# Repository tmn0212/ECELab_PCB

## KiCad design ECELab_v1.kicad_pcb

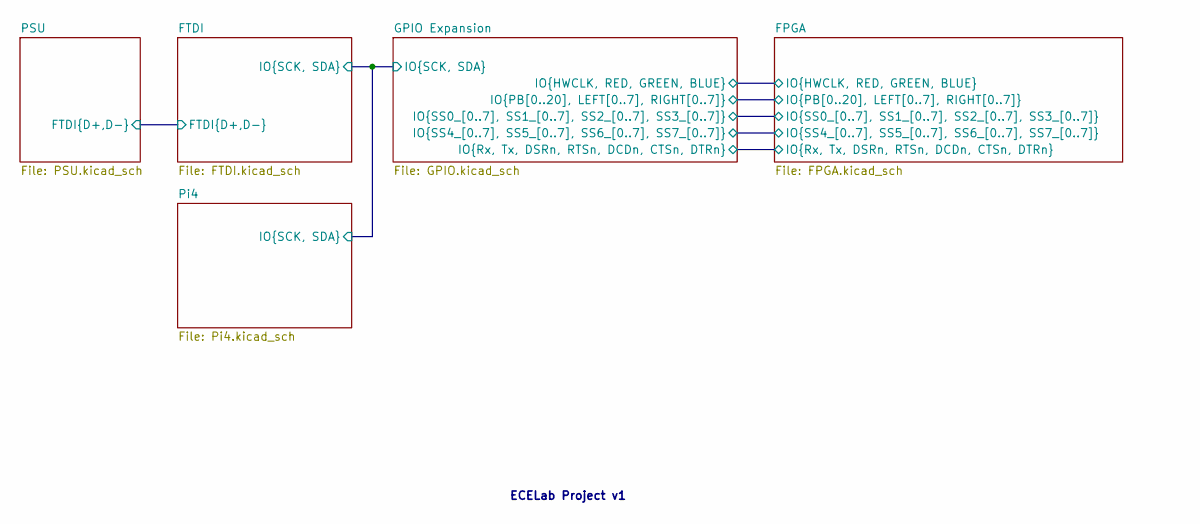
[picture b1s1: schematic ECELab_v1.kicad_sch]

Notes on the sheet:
ECELab Project v1

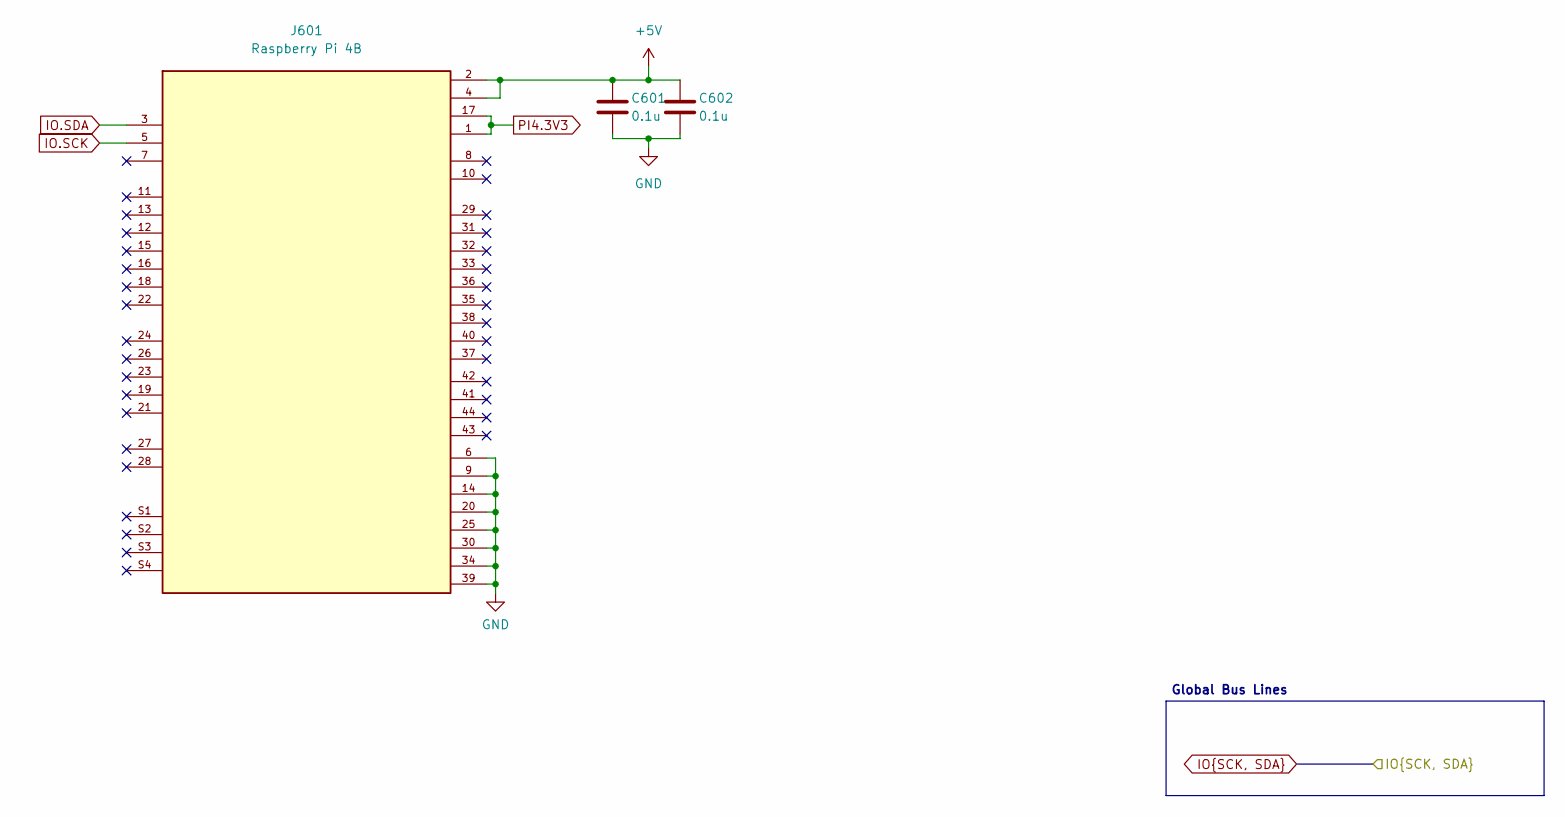
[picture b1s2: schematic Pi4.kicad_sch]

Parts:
C601, C602: 0.1u; C_0402_1005Metric; LCSC Part Number C1525
J601: Raspberry Pi 4B; PinSocket_2x20_P2.54mm_Vertical; LCSC C2977589

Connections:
+5V: C601.1, C602.1, J601.2 (5V), J601.4 (5V); also elsewhere on the board
GND: C601.2, C602.2, J601.6 (GND), J601.9 (GND), J601.14 (GND), J601.20 (GND), J601.25 (GND), J601.30 (GND), J601.34 (GND), J601.39 (GND); also elsewhere on the board
IO.SCK: J601.5 (GPIO3/SCL1); also elsewhere on the board
IO.SDA: J601.3 (GPIO2/SDA1); also elsewhere on the board
PI4.3V3: J601.1 (3V3), J601.17 (3V3); also elsewhere on the board

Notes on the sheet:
Global Bus Lines

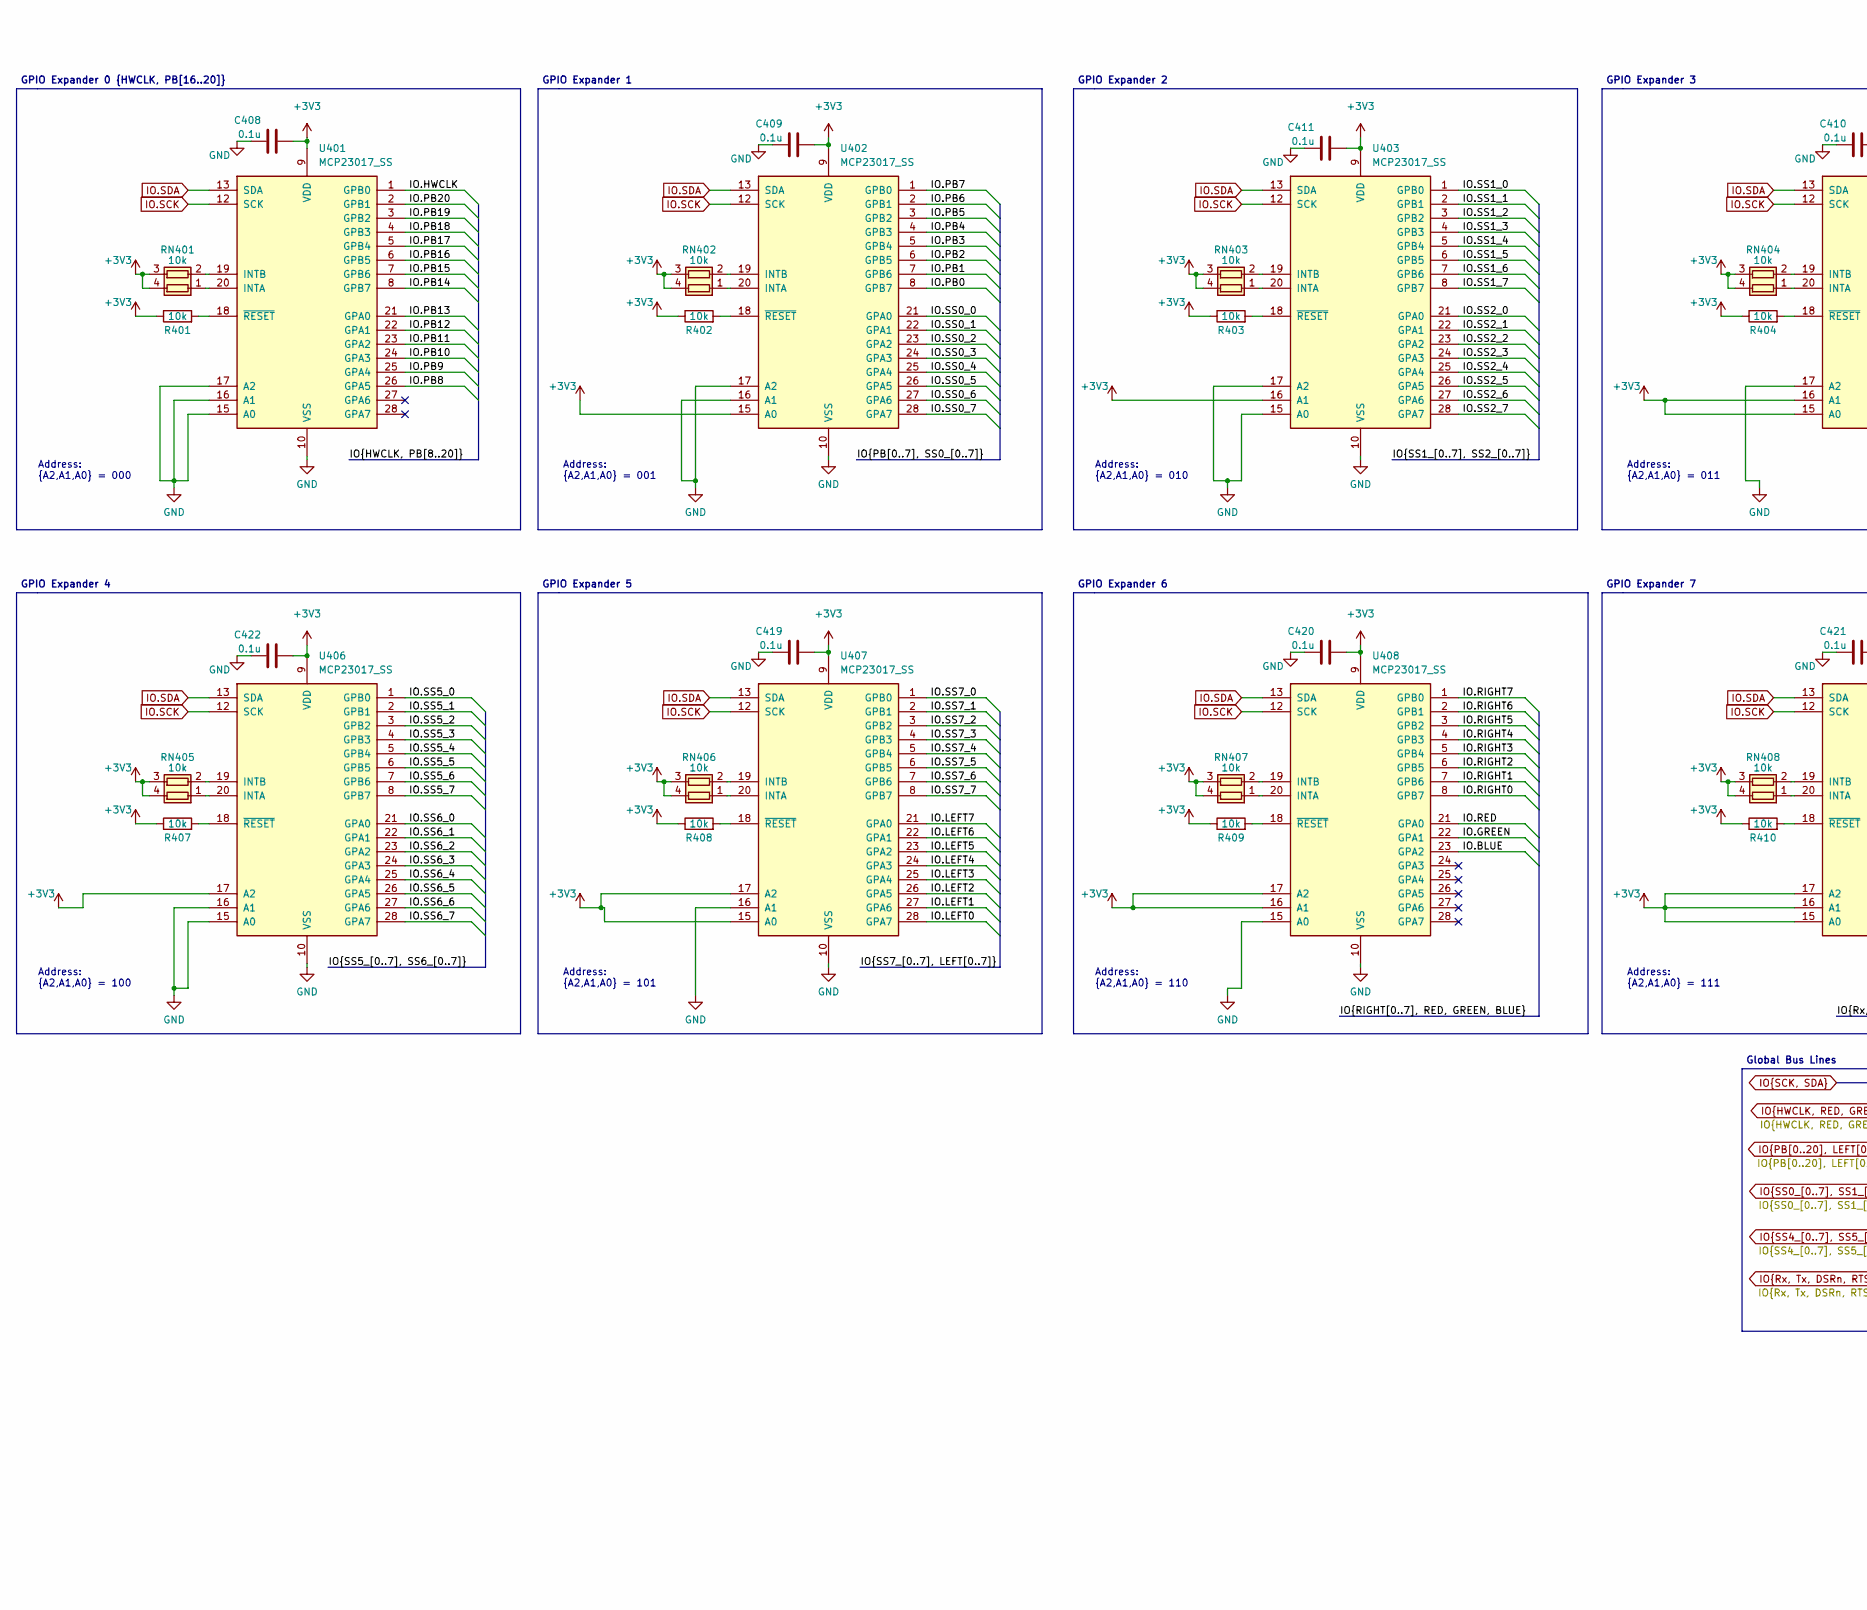
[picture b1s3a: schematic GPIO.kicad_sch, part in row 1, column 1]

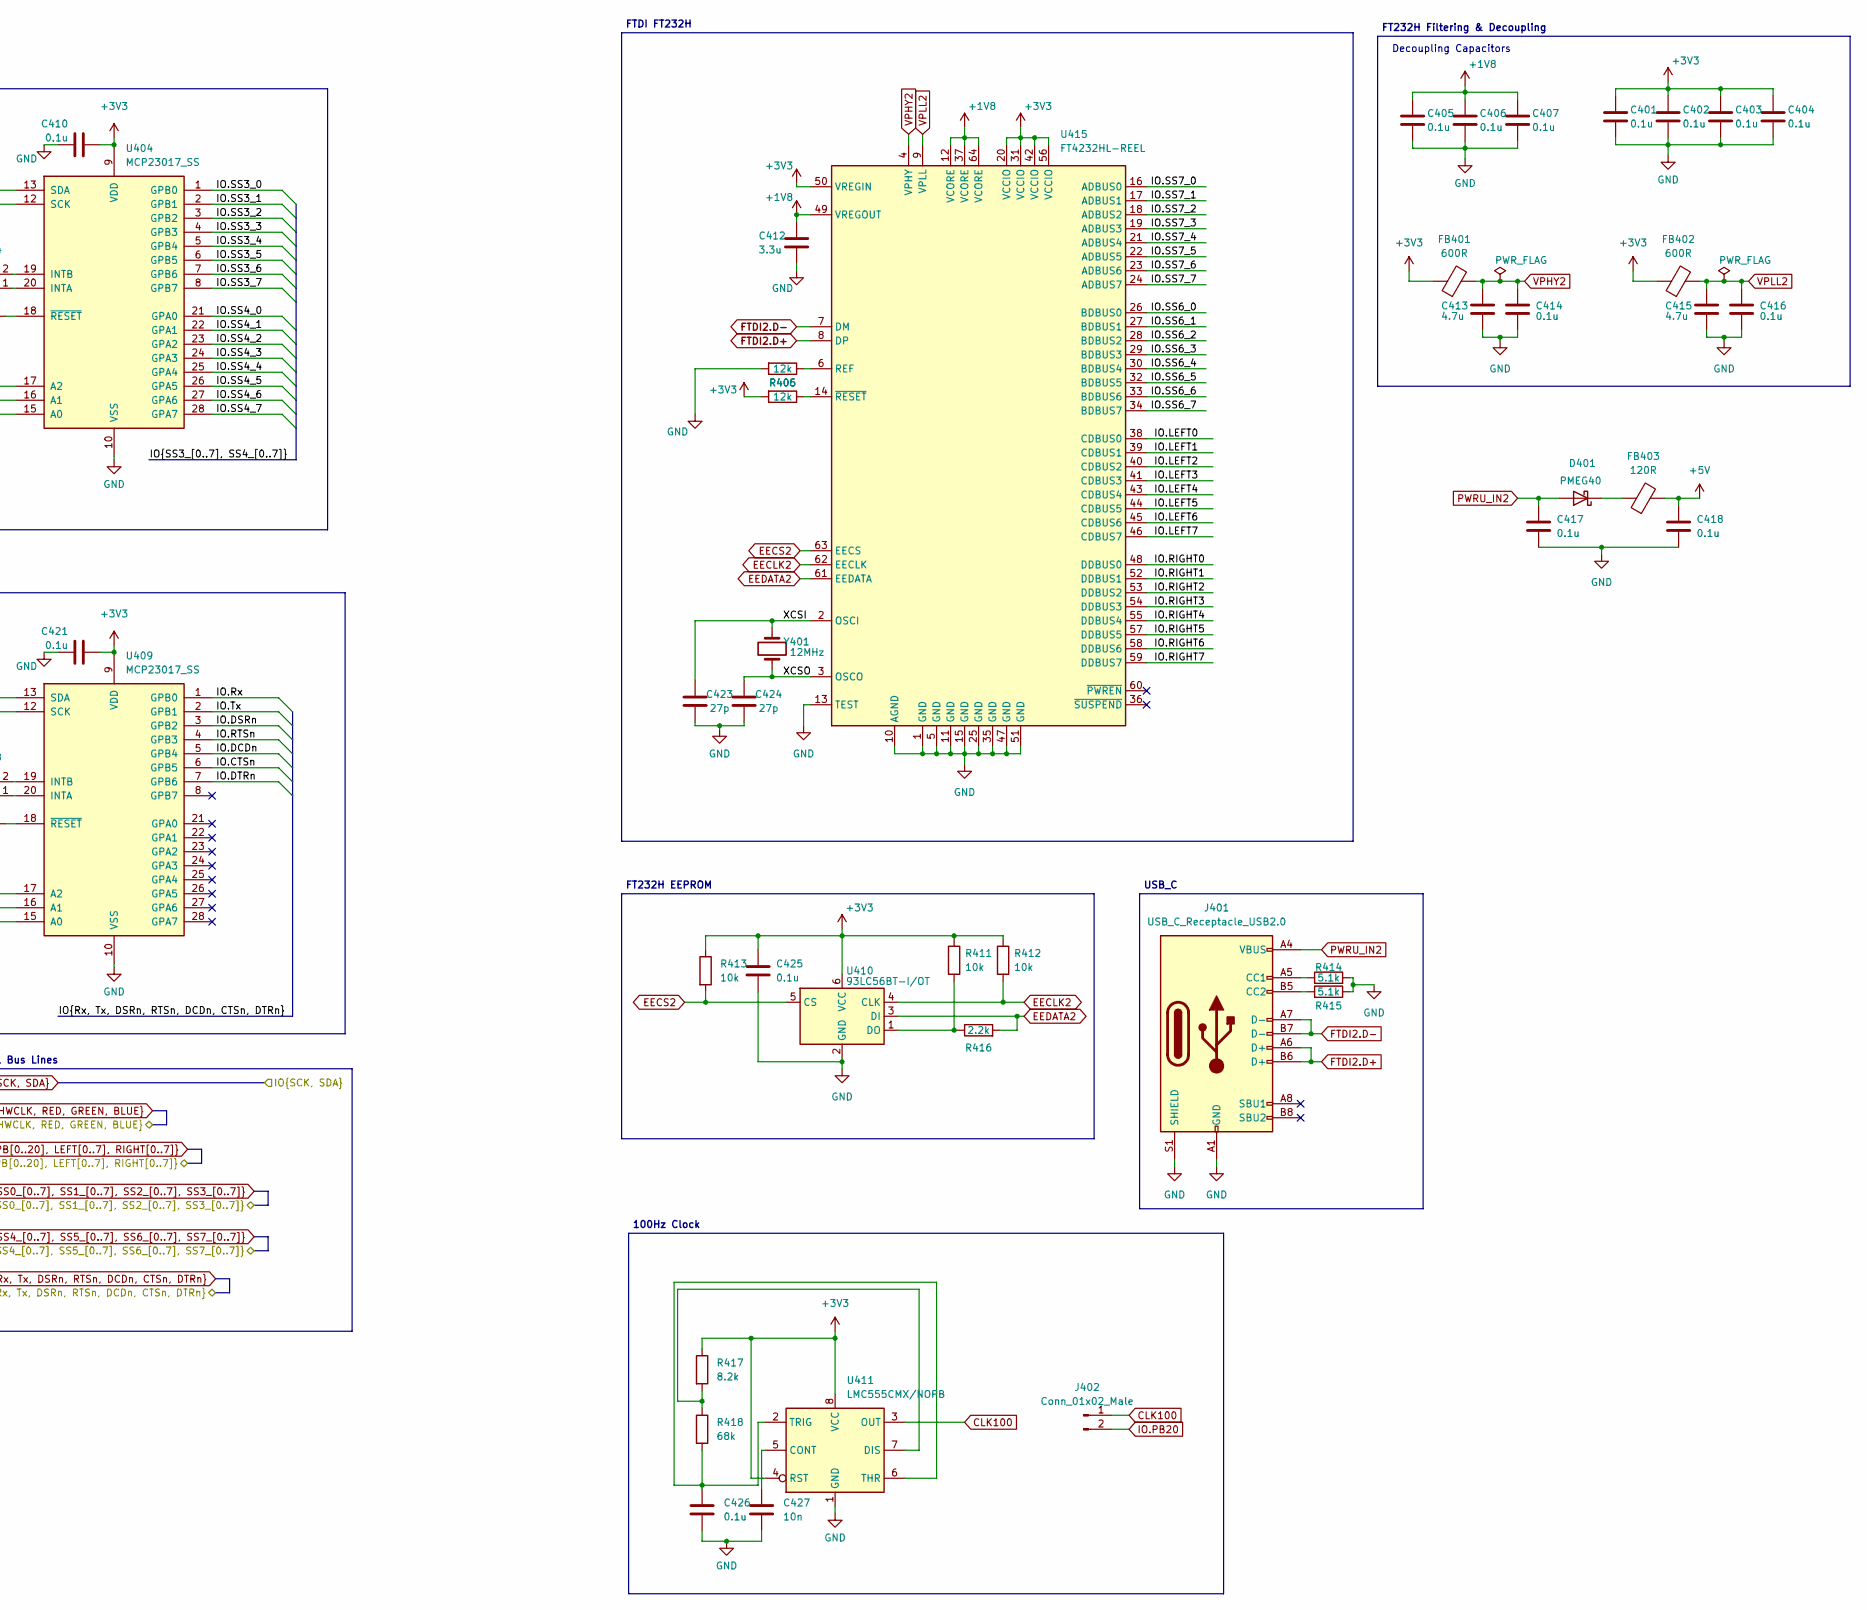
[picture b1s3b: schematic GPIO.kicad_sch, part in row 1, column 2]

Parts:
C401, C402, C403, C404, C405, C406, C407, C408, C409, C410, C411, C417, C418, C419, C420, C421, C422: 0.1u; C_0402_1005Metric; LCSC Part Number C1525
C412: 3.3u; C_0402_1005Metric; LCSC C694161
C413, C415: 4.7u; C_0402_1005Metric; LCSC C368809
C414, C416, C425, C426: 0.1u; C_0402_1005Metric; LCSC C1525
C423, C424: 27p; C_0402_1005Metric; LCSC Part Number C1557
C427: 10n; C_0402_1005Metric; LCSC C60133
D401: PMEG40; D_SOD-323; LCSC Part Number C36975
FB401, FB402: 600R; L_0603_1608Metric; LCSC Part Number C1002
FB403: 120R; L_0603_1608Metric; LCSC Part Number C279682
J401: USB_C_Receptacle_USB2.0; USB_C_Receptacle_HRO_TYPE-C-31-M-12; LCSC Part Number C165948
J402: Conn_01x02_Male; PinHeader_1x02_P2.54mm_Vertical; LCSC C5116481
R401, R402, R403, R404, R407, R408, R409, R410: 10k; R_0402_1005Metric; LCSC Part Number C140214
R405, R406: 12k; R_0402_1005Metric; LCSC Part Number C25752
R411, R412, R413: 10k; R_0402_1005Metric; LCSC C140214
R414, R415: 5.1k; R_0402_1005Metric; LCSC Part Number C105872
R416: 2.2k; R_0402_1005Metric; LCSC Part Number C25879
R417: 8.2k; R_0402_1005Metric; LCSC C103167
R418: 68k; R_0402_1005Metric; LCSC C36871
RN401, RN402, RN403, RN404, RN405, RN406, RN407, RN408: 10k; R_Array_Convex_2x0402; LCSC Part Number C695179
U401, U402, U403, U404, U406, U407, U408, U409: MCP23017_SS; SSOP-28_5.3x10.2mm_P0.65mm; LCSC Part Number C558584
U410: 93LC56BT-I/OT; SOT-23-6; LCSC Part Number C190271
U411: LMC555CMX/NOPB; SOIC-8_3.9x4.9mm_P1.27mm; LCSC C90760
U415: FT4232HL-REEL; LQFP-64_10x10mm_P0.5mm; LCSC C56742
Y401: 12MHz; Crystal_SMD_HC49-SD; LCSC Part Number C14871

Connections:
+1V8: C405.1, C406.1, C407.1, C412.1, U415.12 (VCORE), U415.37 (VCORE), U415.49 (VREGOUT), U415.64 (VCORE); also elsewhere on the board
+5V: C418.1, FB403.2; also elsewhere on the board
/GPIO Expansion/IO.SS4_0: U404.21 (GPA0); also elsewhere on the board
/GPIO Expansion/IO.SS4_1: U404.22 (GPA1); also elsewhere on the board
/GPIO Expansion/IO.SS4_2: U404.23 (GPA2); also elsewhere on the board
/GPIO Expansion/IO.SS4_3: U404.24 (GPA3); also elsewhere on the board
/GPIO Expansion/IO.SS4_4: U404.25 (GPA4); also elsewhere on the board
/GPIO Expansion/IO.SS4_5: U404.26 (GPA5); also elsewhere on the board
/GPIO Expansion/IO.SS4_6: U404.27 (GPA6); also elsewhere on the board
/GPIO Expansion/IO.SS4_7: U404.28 (GPA7); also elsewhere on the board
/GPIO Expansion/IO.SS5_0: U406.1 (GPB0); also elsewhere on the board
/GPIO Expansion/IO.SS5_1: U406.2 (GPB1); also elsewhere on the board
/GPIO Expansion/IO.SS5_2: U406.3 (GPB2); also elsewhere on the board
/GPIO Expansion/IO.SS5_3: U406.4 (GPB3); also elsewhere on the board
/GPIO Expansion/IO.SS5_4: U406.5 (GPB4); also elsewhere on the board
/GPIO Expansion/IO.SS5_5: U406.6 (GPB5); also elsewhere on the board
/GPIO Expansion/IO.SS5_6: U406.7 (GPB6); also elsewhere on the board
/GPIO Expansion/IO.SS5_7: U406.8 (GPB7); also elsewhere on the board
/GPIO Expansion/IO.SS6_0: U406.21 (GPA0), U415.26 (BDBUS0); also elsewhere on the board
/GPIO Expansion/IO.SS6_1: U406.22 (GPA1), U415.27 (BDBUS1); also elsewhere on the board
/GPIO Expansion/IO.SS6_2: U406.23 (GPA2), U415.28 (BDBUS2); also elsewhere on the board
/GPIO Expansion/IO.SS6_3: U406.24 (GPA3), U415.29 (BDBUS3); also elsewhere on the board
/GPIO Expansion/IO.SS6_4: U406.25 (GPA4), U415.30 (BDBUS4); also elsewhere on the board
/GPIO Expansion/IO.SS6_5: U406.26 (GPA5), U415.32 (BDBUS5); also elsewhere on the board
/GPIO Expansion/IO.SS6_6: U406.27 (GPA6), U415.33 (BDBUS6); also elsewhere on the board
/GPIO Expansion/IO.SS6_7: U406.28 (GPA7), U415.34 (BDBUS7); also elsewhere on the board
/GPIO Expansion/IO.SS7_0: U407.1 (GPB0), U415.16 (ADBUS0); also elsewhere on the board
/GPIO Expansion/IO.SS7_1: U407.2 (GPB1), U415.17 (ADBUS1); also elsewhere on the board
/GPIO Expansion/IO.SS7_2: U407.3 (GPB2), U415.18 (ADBUS2); also elsewhere on the board
/GPIO Expansion/IO.SS7_3: U407.4 (GPB3), U415.19 (ADBUS3); also elsewhere on the board
/GPIO Expansion/IO.SS7_4: U407.5 (GPB4), U415.21 (ADBUS4); also elsewhere on the board
/GPIO Expansion/IO.SS7_5: U407.6 (GPB5), U415.22 (ADBUS5); also elsewhere on the board
/GPIO Expansion/IO.SS7_6: U407.7 (GPB6), U415.23 (ADBUS6); also elsewhere on the board
/GPIO Expansion/IO.SS7_7: U407.8 (GPB7), U415.24 (ADBUS7); also elsewhere on the board
/GPIO Expansion/XCSI: C423.2, U415.2 (OSCI), Y401.1
/GPIO Expansion/XCSO: C424.2, U415.3 (OSCO), Y401.2
CLK100: J402.1, U411.3 (OUT)
EECLK2: R412.2, U410.4 (CLK), U415.62 (EECLK)
EECS2: R413.2, U410.5 (CS), U415.63 (EECS)
EEDATA2: R416.2, U410.3 (DI), U415.61 (EEDATA)
FTDI2.D+: J401.A6 (D+), J401.B6 (D+), U415.8 (DP)
FTDI2.D-: J401.A7 (D-), J401.B7 (D-), U415.7 (DM)
GND: C401.2, C402.2, C403.2, C404.2, C405.2, C406.2, C407.2, C408.1, C409.1, C410.1, C411.1, C412.2, C413.2, C414.2, C415.2, C416.2, C417.2, C418.2, C419.1, C420.1, C421.1, C422.1, C423.1, C424.1, C425.2, C426.2, C427.2, J401.A1 (GND), J401.A12 (GND), J401.B1 (GND), J401.B12 (GND), J401.S1 (SHIELD), R405.2, R414.2, R415.1, U401.10 (VSS), U401.15 (A0), U401.16 (A1), U401.17 (A2), U402.10 (VSS), U402.16 (A1), U402.17 (A2), U403.10 (VSS), U403.15 (A0), U403.17 (A2), U404.10 (VSS), U404.17 (A2), U406.10 (VSS), U406.15 (A0), U406.16 (A1), U407.10 (VSS), U407.16 (A1), U408.10 (VSS), U408.15 (A0), U409.10 (VSS), U410.2 (GND), U411.1 (GND), U415.1 (GND), U415.5 (GND), U415.10 (AGND), U415.11 (GND), U415.13 (TEST), U415.15 (GND), U415.25 (GND), U415.35 (GND), U415.47 (GND), U415.51 (GND); also elsewhere on the board
IO.BLUE: U408.23 (GPA2); also elsewhere on the board
IO.CTSn: U409.6 (GPB5); also elsewhere on the board
IO.DCDn: U409.5 (GPB4); also elsewhere on the board
IO.DSRn: U409.3 (GPB2); also elsewhere on the board
IO.DTRn: U409.7 (GPB6); also elsewhere on the board
IO.GREEN: U408.22 (GPA1); also elsewhere on the board
IO.HWCLK: U401.1 (GPB0); also elsewhere on the board
IO.LEFT0: U407.28 (GPA7), U415.38 (CDBUS0); also elsewhere on the board
IO.LEFT1: U407.27 (GPA6), U415.39 (CDBUS1); also elsewhere on the board
IO.LEFT2: U407.26 (GPA5), U415.40 (CDBUS2); also elsewhere on the board
IO.LEFT3: U407.25 (GPA4), U415.41 (CDBUS3); also elsewhere on the board
IO.LEFT4: U407.24 (GPA3), U415.43 (CDBUS4); also elsewhere on the board
IO.LEFT5: U407.23 (GPA2), U415.44 (CDBUS5); also elsewhere on the board
IO.LEFT6: U407.22 (GPA1), U415.45 (CDBUS6); also elsewhere on the board
IO.LEFT7: U407.21 (GPA0), U415.46 (CDBUS7); also elsewhere on the board
IO.PB0: U402.8 (GPB7); also elsewhere on the board
IO.PB1: U402.7 (GPB6); also elsewhere on the board
IO.PB2: U402.6 (GPB5); also elsewhere on the board
IO.PB3: U402.5 (GPB4); also elsewhere on the board
IO.PB4: U402.4 (GPB3); also elsewhere on the board
IO.PB5: U402.3 (GPB2); also elsewhere on the board
IO.PB6: U402.2 (GPB1); also elsewhere on the board
IO.PB7: U402.1 (GPB0); also elsewhere on the board
IO.PB8: U401.26 (GPA5); also elsewhere on the board
IO.PB9: U401.25 (GPA4); also elsewhere on the board
IO.PB10: U401.24 (GPA3); also elsewhere on the board
IO.PB11: U401.23 (GPA2); also elsewhere on the board
IO.PB12: U401.22 (GPA1); also elsewhere on the board
IO.PB13: U401.21 (GPA0); also elsewhere on the board
IO.PB14: U401.8 (GPB7); also elsewhere on the board
IO.PB15: U401.7 (GPB6); also elsewhere on the board
IO.PB16: U401.6 (GPB5); also elsewhere on the board
IO.PB17: U401.5 (GPB4); also elsewhere on the board
IO.PB18: U401.4 (GPB3); also elsewhere on the board
IO.PB19: U401.3 (GPB2); also elsewhere on the board
IO.PB20: J402.2, U401.2 (GPB1); also elsewhere on the board
IO.RED: U408.21 (GPA0); also elsewhere on the board
IO.RIGHT0: U408.8 (GPB7), U415.48 (DDBUS0); also elsewhere on the board
IO.RIGHT1: U408.7 (GPB6), U415.52 (DDBUS1); also elsewhere on the board
IO.RIGHT2: U408.6 (GPB5), U415.53 (DDBUS2); also elsewhere on the board
IO.RIGHT3: U408.5 (GPB4), U415.54 (DDBUS3); also elsewhere on the board
IO.RIGHT4: U408.4 (GPB3), U415.55 (DDBUS4); also elsewhere on the board
IO.RIGHT5: U408.3 (GPB2), U415.57 (DDBUS5); also elsewhere on the board
IO.RIGHT6: U408.2 (GPB1), U415.58 (DDBUS6); also elsewhere on the board
IO.RIGHT7: U408.1 (GPB0), U415.59 (DDBUS7); also elsewhere on the board
IO.RTSn: U409.4 (GPB3); also elsewhere on the board
IO.Rx: U409.1 (GPB0); also elsewhere on the board
IO.SCK: U401.12 (SCK), U402.12 (SCK), U403.12 (SCK), U404.12 (SCK), U406.12 (SCK), U407.12 (SCK), U408.12 (SCK), U409.12 (SCK); also elsewhere on the board
IO.SDA: U401.13 (SDA), U402.13 (SDA), U403.13 (SDA), U404.13 (SDA), U406.13 (SDA), U407.13 (SDA), U408.13 (SDA), U409.13 (SDA); also elsewhere on the board
IO.SS0_0: U402.21 (GPA0); also elsewhere on the board
IO.SS0_1: U402.22 (GPA1); also elsewhere on the board
IO.SS0_2: U402.23 (GPA2); also elsewhere on the board
IO.SS0_3: U402.24 (GPA3); also elsewhere on the board
IO.SS0_4: U402.25 (GPA4); also elsewhere on the board
IO.SS0_5: U402.26 (GPA5); also elsewhere on the board
IO.SS0_6: U402.27 (GPA6); also elsewhere on the board
IO.SS0_7: U402.28 (GPA7); also elsewhere on the board
IO.SS1_0: U403.1 (GPB0); also elsewhere on the board
IO.SS1_1: U403.2 (GPB1); also elsewhere on the board
IO.SS1_2: U403.3 (GPB2); also elsewhere on the board
IO.SS1_3: U403.4 (GPB3); also elsewhere on the board
IO.SS1_4: U403.5 (GPB4); also elsewhere on the board
IO.SS1_5: U403.6 (GPB5); also elsewhere on the board
IO.SS1_6: U403.7 (GPB6); also elsewhere on the board
IO.SS1_7: U403.8 (GPB7); also elsewhere on the board
IO.SS2_0: U403.21 (GPA0); also elsewhere on the board
IO.SS2_1: U403.22 (GPA1); also elsewhere on the board
IO.SS2_2: U403.23 (GPA2); also elsewhere on the board
IO.SS2_3: U403.24 (GPA3); also elsewhere on the board
IO.SS2_4: U403.25 (GPA4); also elsewhere on the board
IO.SS2_5: U403.26 (GPA5); also elsewhere on the board
IO.SS2_6: U403.27 (GPA6); also elsewhere on the board
IO.SS2_7: U403.28 (GPA7); also elsewhere on the board
IO.SS3_0: U404.1 (GPB0); also elsewhere on the board
IO.SS3_1: U404.2 (GPB1); also elsewhere on the board
IO.SS3_2: U404.3 (GPB2); also elsewhere on the board
IO.SS3_3: U404.4 (GPB3); also elsewhere on the board
IO.SS3_4: U404.5 (GPB4); also elsewhere on the board
IO.SS3_5: U404.6 (GPB5); also elsewhere on the board
IO.SS3_6: U404.7 (GPB6); also elsewhere on the board
IO.SS3_7: U404.8 (GPB7); also elsewhere on the board
IO.Tx: U409.2 (GPB1); also elsewhere on the board
unnamed: C426.1, R418.2, U411.2 (TRIG), U411.6 (THR)
unnamed: C427.1, U411.5 (CONT)
unnamed: D401.1 (K), FB403.1
unnamed: J401.A5 (CC1), R414.1
unnamed: J401.B5 (CC2), R415.2
unnamed: R401.2, U401.18 (~RESET)
unnamed: R402.2, U402.18 (~RESET)
unnamed: R403.2, U403.18 (~RESET)
unnamed: R404.2, U404.18 (~RESET)
unnamed: R405.1, U415.6 (REF)
unnamed: R406.1, U415.14 (~RESET)
unnamed: R407.2, U406.18 (~RESET)
unnamed: R408.2, U407.18 (~RESET)
unnamed: R409.2, U408.18 (~RESET)
unnamed: R410.2, U409.18 (~RESET)
unnamed: R411.2, R416.1, U410.1 (DO)
unnamed: R417.2, R418.1, U411.7 (DIS)
unnamed: RN401.1 (R1.1), U401.20 (INTA)
unnamed: RN401.2 (R2.1), U401.19 (INTB)
unnamed: RN402.1 (R1.1), U402.20 (INTA)
unnamed: RN402.2 (R2.1), U402.19 (INTB)
unnamed: RN403.1 (R1.1), U403.20 (INTA)
unnamed: RN403.2 (R2.1), U403.19 (INTB)
unnamed: RN404.1 (R1.1), U404.20 (INTA)
unnamed: RN404.2 (R2.1), U404.19 (INTB)
unnamed: RN405.1 (R1.1), U406.20 (INTA)
unnamed: RN405.2 (R2.1), U406.19 (INTB)
unnamed: RN406.1 (R1.1), U407.20 (INTA)
unnamed: RN406.2 (R2.1), U407.19 (INTB)
unnamed: RN407.1 (R1.1), U408.20 (INTA)
unnamed: RN407.2 (R2.1), U408.19 (INTB)
unnamed: RN408.1 (R1.1), U409.20 (INTA)
unnamed: RN408.2 (R2.1), U409.19 (INTB)
PWRU_IN2: C417.1, D401.2 (A), J401.A4 (VBUS), J401.A9 (VBUS), J401.B4 (VBUS), J401.B9 (VBUS)
VPHY2: C413.1, C414.1, FB401.2, U415.4 (VPHY)
VPLL2: C415.1, C416.1, FB402.2, U415.9 (VPLL)

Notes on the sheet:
Decoupling Capacitors
Address: {A2,A1,A0} = 101
GPIO Expander 0 {HWCLK, PB[16..20]}
FT232H Filtering & Decoupling
Address: {A2,A1,A0} = 010
GPIO Expander 6
GPIO Expander 7
GPIO Expander 3
Address: {A2,A1,A0} = 000
Global Bus Lines
Address: {A2,A1,A0} = 110
Address: {A2,A1,A0} = 011
100Hz Clock
GPIO Expander 1
GPIO Expander 2
Address: {A2,A1,A0} = 111
GPIO Expander 5
FT232H EEPROM
GPIO Expander 4
FTDI FT232H
Address: {A2,A1,A0} = 001
Address: {A2,A1,A0} = 100
USB_C

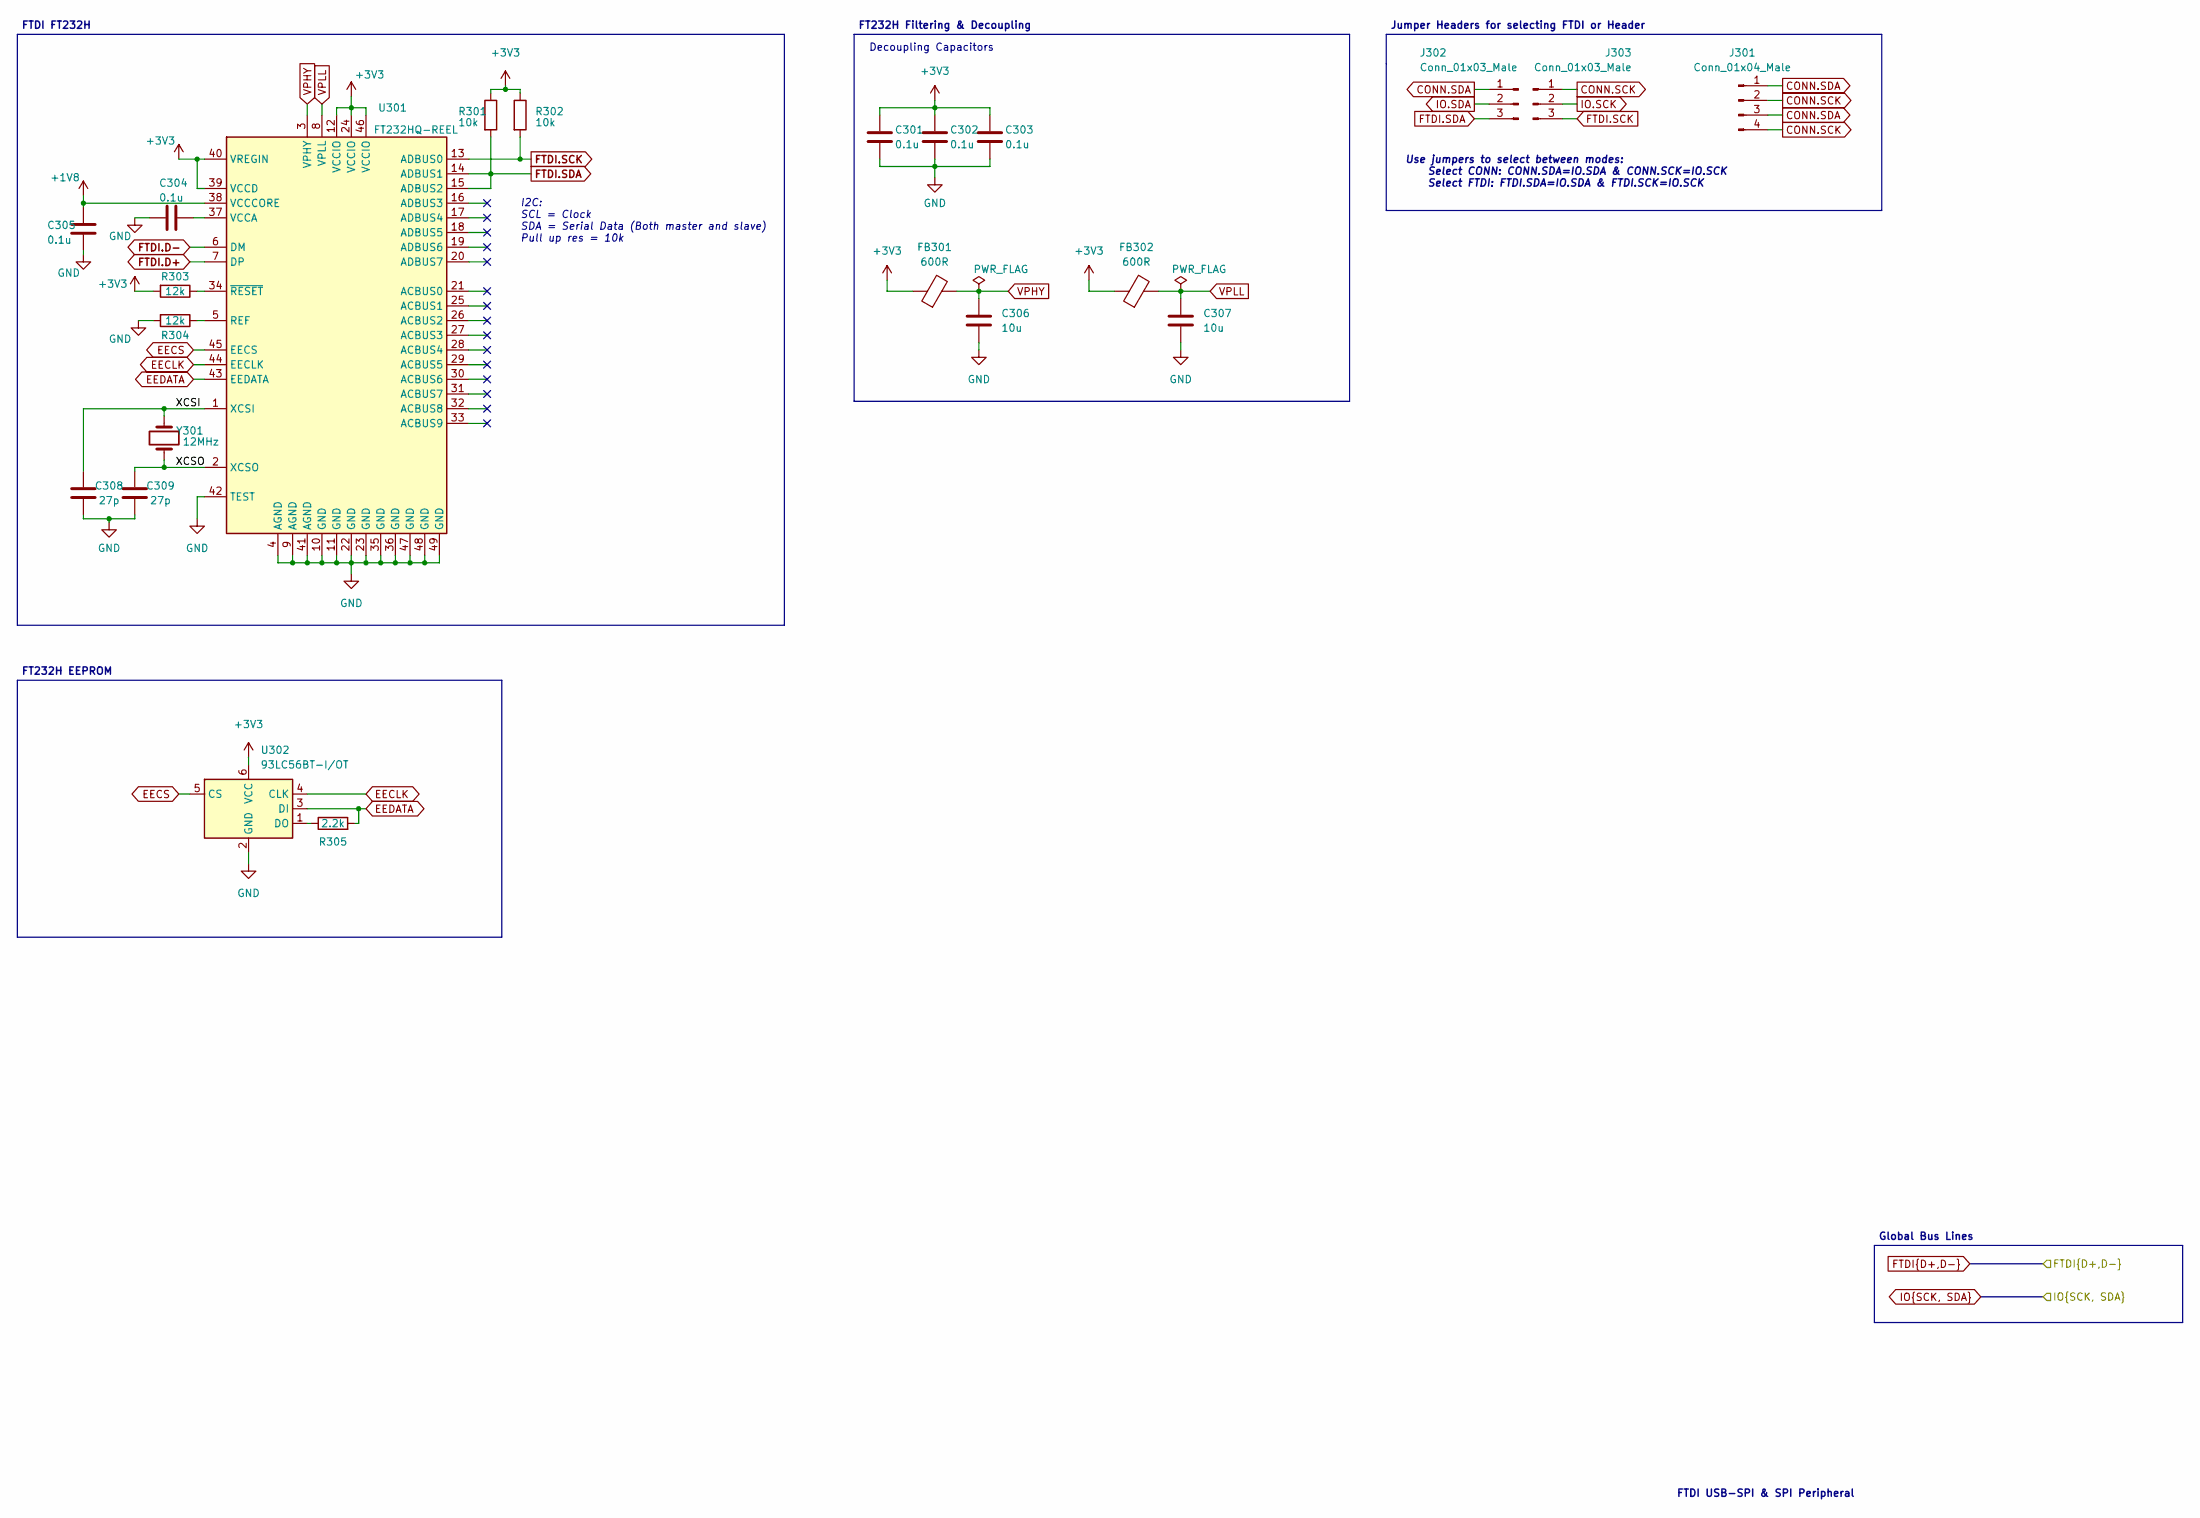
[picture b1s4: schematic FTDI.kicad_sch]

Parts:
C301, C302, C303, C304, C305: 0.1u; C_0402_1005Metric; LCSC Part Number C1525
C306, C307: 10u; C_0402_1005Metric; LCSC Part Number C76991
C308, C309: 27p; C_0402_1005Metric; LCSC Part Number C1557
FB301, FB302: 600R; L_0603_1608Metric; LCSC Part Number C1002
J301: Conn_01x04_Male; PinHeader_1x04_P2.54mm_Horizontal; LCSC C91552
J302, J303: Conn_01x03_Male; PinHeader_1x03_P2.54mm_Vertical; LCSC C3012205
R301, R302: 10k; R_0402_1005Metric; LCSC Part Number C140214
R303, R304: 12k; R_0402_1005Metric; LCSC Part Number C25752
R305: 2.2k; R_0402_1005Metric; LCSC Part Number C25879
U301: FT232HQ-REEL; QFN-48-1EP_8x8mm_P0.5mm_EP6.2x6.2mm; LCSC Part Number C82158
U302: 93LC56BT-I/OT; SOT-23-6; LCSC Part Number C190271
Y301: 12MHz; Crystal_SMD_HC49-SD; LCSC Part Number C14871

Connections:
+1V8: C305.2, U301.38 (VCCCORE); also elsewhere on the board
/FTDI/XCSI: C308.2, U301.1 (XCSI), Y301.1
/FTDI/XCSO: C309.2, U301.2 (XCSO), Y301.2
CONN.SCK: J301.2, J301.4, J303.1
CONN.SDA: J301.1, J301.3, J302.1
EECLK: U301.44 (EECLK), U302.4 (CLK)
EECS: U301.45 (EECS), U302.5 (CS)
EEDATA: R305.2, U301.43 (EEDATA), U302.3 (DI)
FTDI.D+: U301.7 (DP); also elsewhere on the board
FTDI.D-: U301.6 (DM); also elsewhere on the board
FTDI.SCK: J303.3, R302.2, U301.13 (ADBUS0)
FTDI.SDA: J302.3, R301.2, U301.14 (ADBUS1), U301.15 (ADBUS2)
GND: C301.2, C302.2, C303.2, C304.1, C305.1, C306.2, C307.2, C308.1, C309.1, R304.2, U301.4 (AGND), U301.9 (AGND), U301.10 (GND), U301.11 (GND), U301.22 (GND), U301.23 (GND), U301.35 (GND), U301.36 (GND), U301.41 (AGND), U301.42 (TEST), U301.47 (GND), U301.48 (GND), U301.49 (GND), U302.2 (GND); also elsewhere on the board
IO.SCK: J303.2; also elsewhere on the board
IO.SDA: J302.2; also elsewhere on the board
unnamed: C304.2, U301.37 (VCCA)
unnamed: R303.1, U301.34 (~RESET)
unnamed: R304.1, U301.5 (REF)
unnamed: R305.1, U302.1 (DO)
VPHY: C306.1, FB301.2, U301.3 (VPHY)
VPLL: C307.1, FB302.2, U301.8 (VPLL)

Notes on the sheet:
FT232H Filtering & Decoupling
I2C: SCL = Clock SDA = Serial Data (Both master and slave) Pull up res = 10k
FT232H EEPROM
Decoupling Capacitors
Global Bus Lines
FTDI FT232H
Use jumpers to select between modes: Select CONN: CONN.SDA=IO.SDA & CONN.SCK=IO.SCK Select FTDI: FTDI.SDA=IO.SDA & FTDI.SCK=IO.SCK
Jumper Headers for selecting FTDI or Header
FTDI USB-SPI & SPI Peripheral
